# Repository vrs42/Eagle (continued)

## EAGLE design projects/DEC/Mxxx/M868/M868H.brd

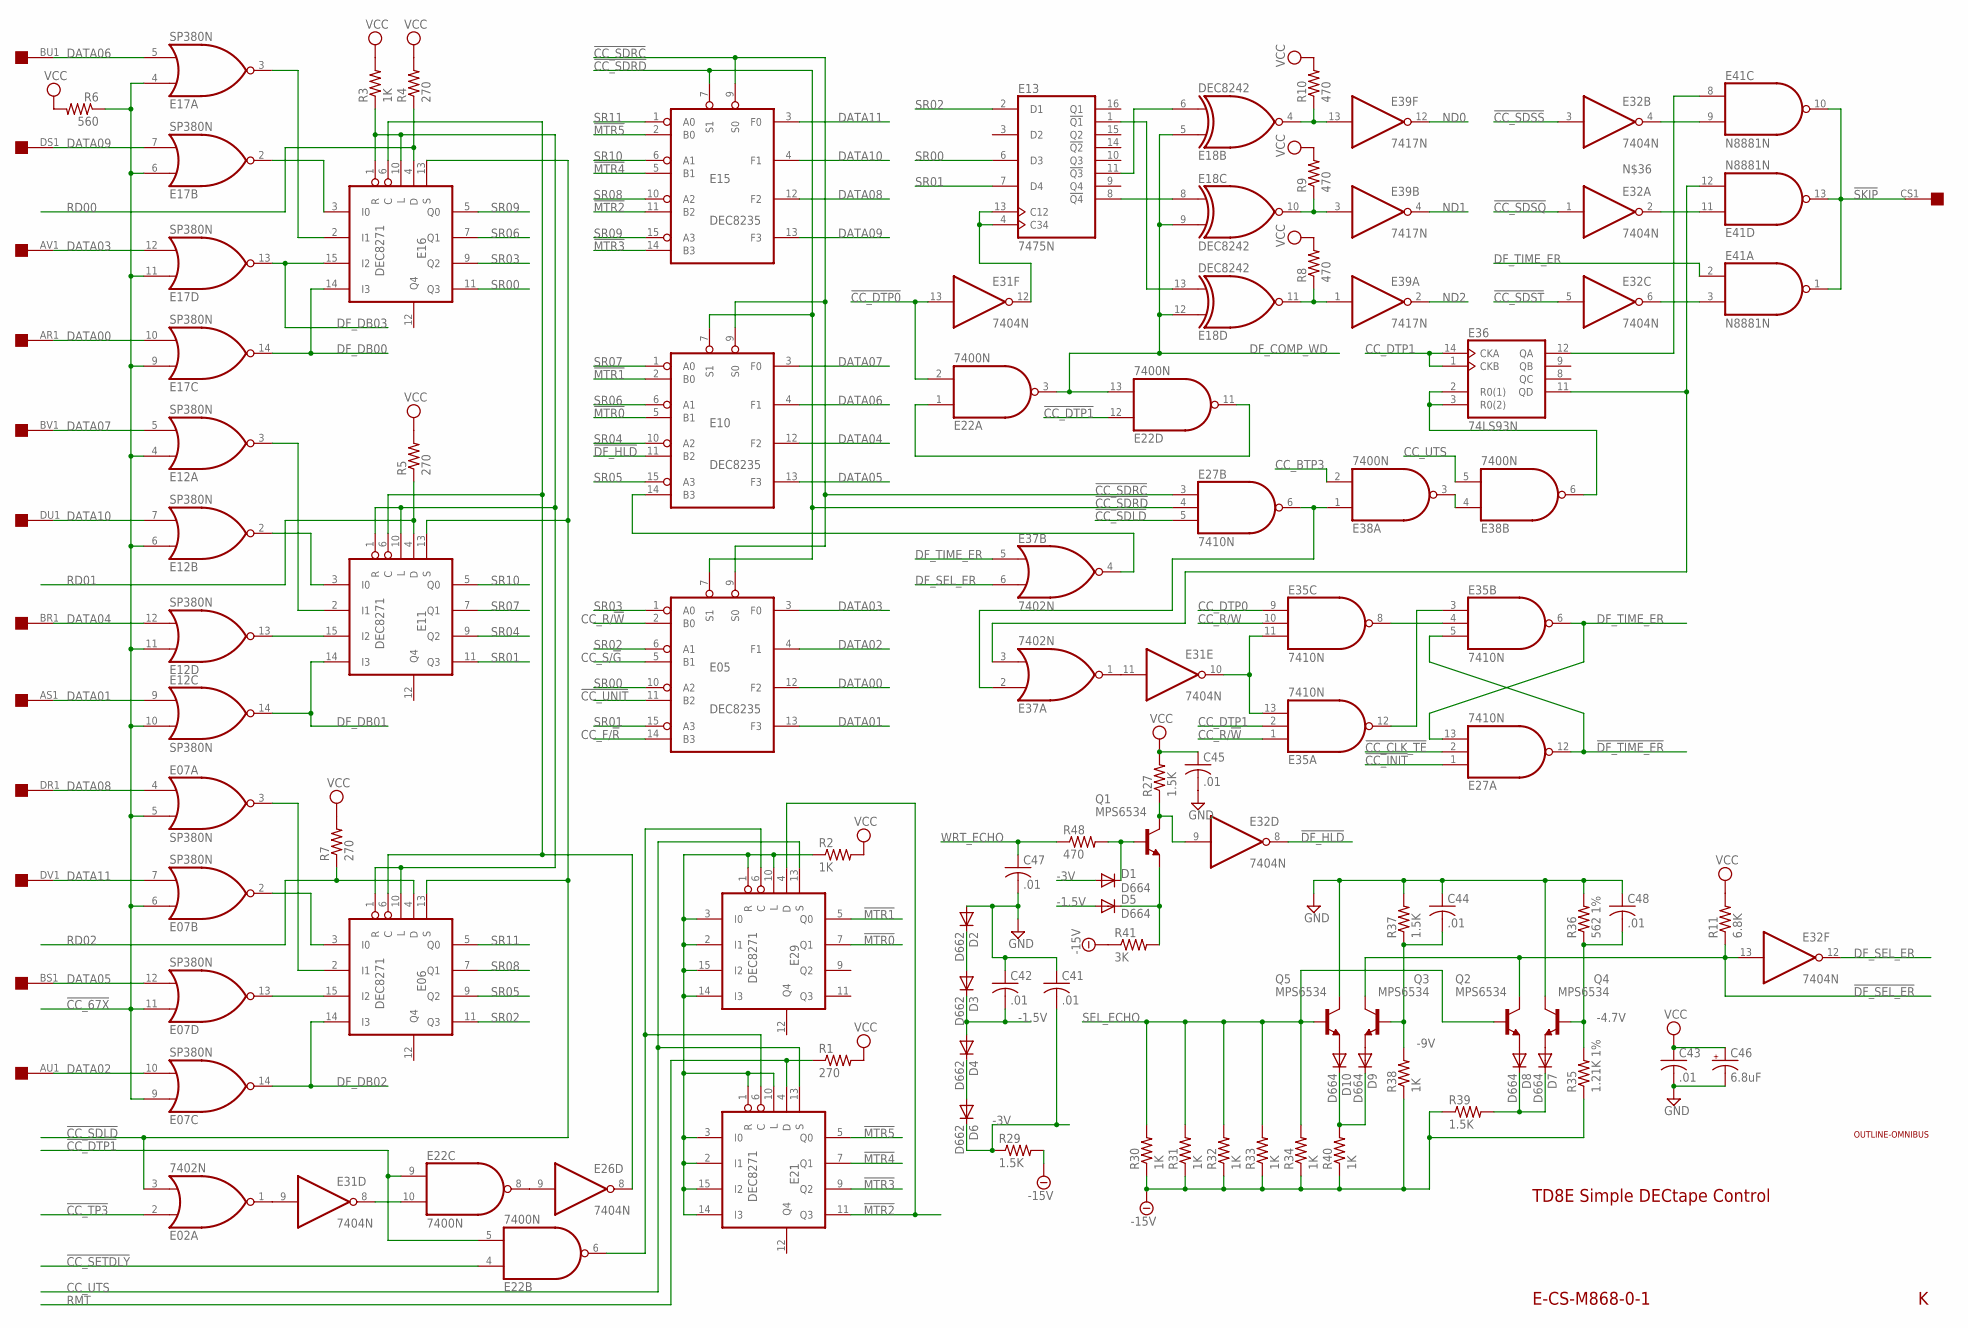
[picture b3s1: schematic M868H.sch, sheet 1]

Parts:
C41, C42, C43, C44, C45, C47, C48: .01; C050-025X075
C46: 6.8uF; E12-8
D1, D5, D7, D8, D9, D10: D664; DO35-10
D2, D3, D4, D6: D662; DO35-10
E02, E37: 7402N; DIL14
E05, E10, E15: DEC8235; DIL16
E06, E11, E16, E21, E29: DEC8271; DIL16
E07, E12, E17: SP380N; DIL14
E13: 7475N; DIL16
E18: DEC8242; DIL14
E22, E38: 7400N; DIL14
E26, E31, E32: 7404N; DIL14
E27, E35: 7410N; DIL14
E36: 74LS93N; DIL14
E39: 7417N; DIL14
E41: N8881N; DIL14
EDGE$: QUAD; EDGE-CON8
Q1, Q2, Q3, Q4, Q5: MPS6534; TO5
R1, R4, R5, R7: 270; 0207/10
R2, R3, R30, R31, R32, R33, R34, R38, R40: 1K; 0207/10
R6: 560; 0207/10
R8, R9, R10, R48: 470; 0207/10
R11: 6.8K; 0207/10
R27, R29, R37, R39: 1.5K; 0207/10
R35: 1.21K 1%; 0207/15
R36: 562 1%; 0207/15
R41: 3K; 0207/10
U$1: OUTLINE-OMNIBUS; OMNIBUS

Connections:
!CC_67X: E07.5 (I1), E07.6 (I0), E07.9 (I0), E07.11 (I0), E12.4 (I0), E12.6 (I0), E12.10 (I1), E12.11 (I0), E17.4 (I0), E17.6 (I0), E17.9 (I0), E17.11 (I0), R6.1; also elsewhere on the board
!CC_CLK_TE: E27.2 (I1); also elsewhere on the board
!CC_DTP0: E22.2 (I1), E31.13 (I); also elsewhere on the board
!CC_DTP1: E22.5 (I1), E22.9 (I0), E22.12 (I0); also elsewhere on the board
!CC_INIT: E27.1 (I0); also elsewhere on the board
!CC_SDLD: E02.3 (I1), E06.13 (S), E11.13 (S), E16.13 (S), E27.5 (I2); also elsewhere on the board
!CC_SDRC: E05.9 (S0), E10.9 (S0), E15.9 (S0), E27.3 (I0); also elsewhere on the board
!CC_SDRD: E05.7 (S1), E10.7 (S1), E15.7 (S1), E27.4 (I1); also elsewhere on the board
!CC_SDSQ: E32.1 (I); also elsewhere on the board
!CC_SDSS: E32.3 (I); also elsewhere on the board
!CC_SDST: E32.5 (I); also elsewhere on the board
!CC_SETDLY: E22.4 (I0); also elsewhere on the board
!CC_TP3: E02.2 (I0); also elsewhere on the board
!CC_UNIT: E05.11 (B2); also elsewhere on the board
!DF_HLD: E10.11 (B2), E32.8 (O); also elsewhere on the board
!DF_SEL_ER: E32.13 (I), Q2.3 (C), Q3.3 (C), R11.1; also elsewhere on the board
!DF_TIME_ER: E27.12 (O), E35.5 (I2); also elsewhere on the board
!MTR0: E10.5 (B1), E29.7 (Q1)
!MTR1: E10.2 (B0), E29.5 (Q0)
!MTR2: E15.11 (B2), E21.11 (Q3), E29.4 (D)
!MTR3: E15.14 (B3), E21.9 (Q2)
!MTR4: E15.5 (B1), E21.7 (Q1)
!MTR5: E15.2 (B0), E21.5 (Q0)
!SKIP: E41.1 (O), E41.10 (O), E41.13 (O), EDGE$.CS1
-1.5V: C42.2, D3.C, D4.A, D5.A
-3V: C41.2, D1.A, D6.C, R29.1
-4.7V: C48.2, Q4.2 (B), R35.2, R36.1
-9V: C44.2, Q3.2 (B), R37.1, R38.2
-15V: R29.2, R30.1, R31.1, R32.1, R33.1, R34.1, R35.1, R38.1, R39.1, R40.1, R41.1; also elsewhere on the board
CC_BTP3: E38.2 (I1); also elsewhere on the board
CC_DTP0: E35.9 (I0); also elsewhere on the board
CC_DTP1: E35.2 (I1), E36.1 (CKB), E36.14 (CKA); also elsewhere on the board
CC_F/!R: E05.14 (B3); also elsewhere on the board
CC_R/!W: E05.2 (B0), E35.1 (I0); also elsewhere on the board
CC_R/W: E35.10 (I1); also elsewhere on the board
CC_S/!G: E05.5 (B1); also elsewhere on the board
CC_UTS: E21.13 (S), E29.13 (S), E38.5 (I1); also elsewhere on the board
DATA00: E05.12 (F2), E17.10 (I1), EDGE$.AR1
DATA01: E05.13 (F3), E12.9 (I0), EDGE$.AS1
DATA02: E05.4 (F1), E07.10 (I1), EDGE$.AU1
DATA03: E05.3 (F0), E17.12 (I1), EDGE$.AV1
DATA04: E10.12 (F2), E12.12 (I1), EDGE$.BR1
DATA05: E07.12 (I1), E10.13 (F3), EDGE$.BS1
DATA06: E10.4 (F1), E17.5 (I1), EDGE$.BU1
DATA07: E10.3 (F0), E12.5 (I1), EDGE$.BV1
DATA08: E07.4 (I0), E15.12 (F2), EDGE$.DR1
DATA09: E15.13 (F3), E17.7 (I1), EDGE$.DS1
DATA10: E12.7 (I1), E15.4 (F1), EDGE$.DU1
DATA11: E07.7 (I1), E15.3 (F0), EDGE$.DV1
DF_COMP_WD: E18.5 (I0), E18.9 (I1), E18.12 (I0), E22.3 (O), E22.13 (I1)
DF_DB00: E16.14 (I3), E17.14 (O); also elsewhere on the board
DF_DB01: E11.14 (I3), E12.14 (O); also elsewhere on the board
DF_DB02: E06.14 (I3), E07.14 (O); also elsewhere on the board
DF_DB03: E16.15 (I2), E17.13 (O); also elsewhere on the board
DF_SEL_ER: E32.12 (O), E37.6 (I1)
DF_TIME_ER: E27.13 (I2), E35.6 (O), E37.5 (I0), E41.2 (I0)
GND: C41.1, C42.1, C43.2, C44.1, C45.2, C46.-, C47.2, C48.1, D2.A, E02.7 (GND), E05.8 (GND), E06.8 (GND), E07.1 (GND), E10.8 (GND), E11.8 (GND), E12.1 (GND), E13.12 (GND), E15.8 (GND), E16.8 (GND), E17.1 (GND), E18.7 (GND), E21.8 (GND), E22.7 (GND), E26.7 (GND), E27.7 (GND), E29.8 (GND), E31.7 (GND), E32.7 (GND), E35.7 (GND), E36.10 (GND), E37.7 (GND), E38.7 (GND), E39.7 (GND), E41.7 (GND), Q4.3 (C), Q5.3 (C), R36.2, R37.2; also elsewhere on the board
unnamed: E06.1 (R), E06.10 (L), E11.1 (R), E11.10 (L), E16.1 (R), E16.10 (L), R3.1
unnamed: E02.1 (O), E31.9 (I)
unnamed: E16.2 (I1), E17.3 (O)
unnamed: E16.3 (I0), E17.2 (O)
unnamed: E21.1 (R), E21.2 (I1), E21.3 (I0), E21.10 (L), E21.14 (I3), E21.15 (I2), E29.1 (R), E29.2 (I1), E29.3 (I0), E29.10 (L), E29.14 (I3), E29.15 (I2), R2.1
unnamed: E06.6 (C), E11.6 (C), E16.6 (C), E26.8 (O)
unnamed: E11.2 (I1), E12.3 (O)
unnamed: E11.3 (I0), E12.2 (O)
unnamed: E13.11 (!Q3), E18.6 (I1)
unnamed: E11.15 (I2), E12.13 (O)
unnamed: E06.2 (I1), E07.3 (O)
unnamed: E06.3 (I0), E07.2 (O)
unnamed: E06.15 (I2), E07.13 (O)
unnamed: E27.6 (O), E37.2 (I0), E38.1 (I0)
unnamed: E36.12 (QA), E41.8 (I0)
unnamed: E22.8 (O), E26.9 (I)
unnamed: E22.10 (I1), E31.8 (O)
unnamed: E21.6 (C), E22.6 (O), E29.6 (C)
unnamed: E13.1 (!Q1), E18.13 (I1)
unnamed: E18.11 (O), E39.1 (I), R8.1
unnamed: E13.8 (!Q4), E18.8 (I0)
unnamed: E13.4 (C34), E13.13 (C12), E31.12 (O)
unnamed: E36.11 (QD), E37.3 (I1), E41.12 (I1)
unnamed: E22.1 (I0), E22.11 (O)
unnamed: E18.10 (O), E39.3 (I), R9.1
unnamed: E18.4 (O), E39.13 (I), R10.1
unnamed: E10.14 (B3), E37.4 (O)
unnamed: E36.2 (R0(1)), E36.3 (R0(2)), E38.6 (O)
unnamed: E38.3 (O), E38.4 (I0)
unnamed: E32.6 (O), E41.3 (I1)
unnamed: E32.2 (O), E41.11 (I0)
unnamed: E32.4 (O), E41.9 (I1)
unnamed: E31.11 (I), E37.1 (O)
unnamed: E31.10 (O), E35.11 (I2), E35.13 (I2)
unnamed: E35.3 (I0), E35.12 (O)
unnamed: E35.4 (I1), E35.8 (O)
unnamed: D1.C, Q1.2 (B), R48.2
unnamed: D5.C, Q1.1 (E), R41.2
unnamed: E32.9 (I), Q1.3 (C), R27.1
unnamed: D2.C, D3.A
unnamed: D9.C, D10.C, R40.2
unnamed: D4.C, D6.A
unnamed: D10.A, Q5.1 (E)
unnamed: D9.A, Q3.1 (E)
unnamed: D8.A, Q2.1 (E)
unnamed: D7.A, Q4.1 (E)
unnamed: D7.C, D8.C, R39.2
ND0: E39.12 (O); also elsewhere on the board
ND1: E39.4 (O); also elsewhere on the board
ND2: E39.2 (O); also elsewhere on the board
RD00: E16.4 (D), R4.1; also elsewhere on the board
RD01: E11.4 (D), R5.1; also elsewhere on the board
RD02: E06.4 (D), R7.1; also elsewhere on the board
RMT: E21.4 (D), R1.1; also elsewhere on the board
SEL_ECHO: Q2.2 (B), Q5.2 (B), R30.2, R31.2, R32.2, R33.2, R34.2; also elsewhere on the board
SR00: E05.10 (A2), E13.6 (D3), E16.11 (Q3)
SR01: E05.15 (A3), E11.11 (Q3), E13.7 (D4)
SR02: E05.6 (A1), E06.11 (Q3), E13.2 (D1)
SR03: E05.1 (A0), E16.9 (Q2)
SR04: E10.10 (A2), E11.9 (Q2)
SR05: E06.9 (Q2), E10.15 (A3)
SR06: E10.6 (A1), E16.7 (Q1)
SR07: E10.1 (A0), E11.7 (Q1)
SR08: E06.7 (Q1), E15.10 (A2)
SR09: E15.15 (A3), E16.5 (Q0)
SR10: E11.5 (Q0), E15.6 (A1)
SR11: E06.5 (Q0), E15.1 (A0)
VCC: C43.1, C45.1, C46.+, E02.14 (VCC), E05.16 (VCC), E06.16 (VCC), E07.8 (VCC), E10.16 (VCC), E11.16 (VCC), E12.8 (VCC), E13.5 (VCC), E15.16 (VCC), E16.16 (VCC), E17.8 (VCC), E18.14 (VCC), E21.16 (VCC), E22.14 (VCC), E26.14 (VCC), E27.14 (VCC), E29.16 (VCC), E31.14 (VCC), E32.14 (VCC), E35.14 (VCC), E36.5 (VCC), E37.14 (VCC), E38.14 (VCC), E39.14 (VCC), E41.14 (VCC), R1.2, R2.2, R3.2, R4.2, R5.2, R6.2, R7.2, R8.2, R9.2, R10.2, R11.2, R27.2; also elsewhere on the board
WRT_ECHO: C47.1, R48.1; also elsewhere on the board

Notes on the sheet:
E-CS-M868-0-1
TD8E Simple DECtape Control

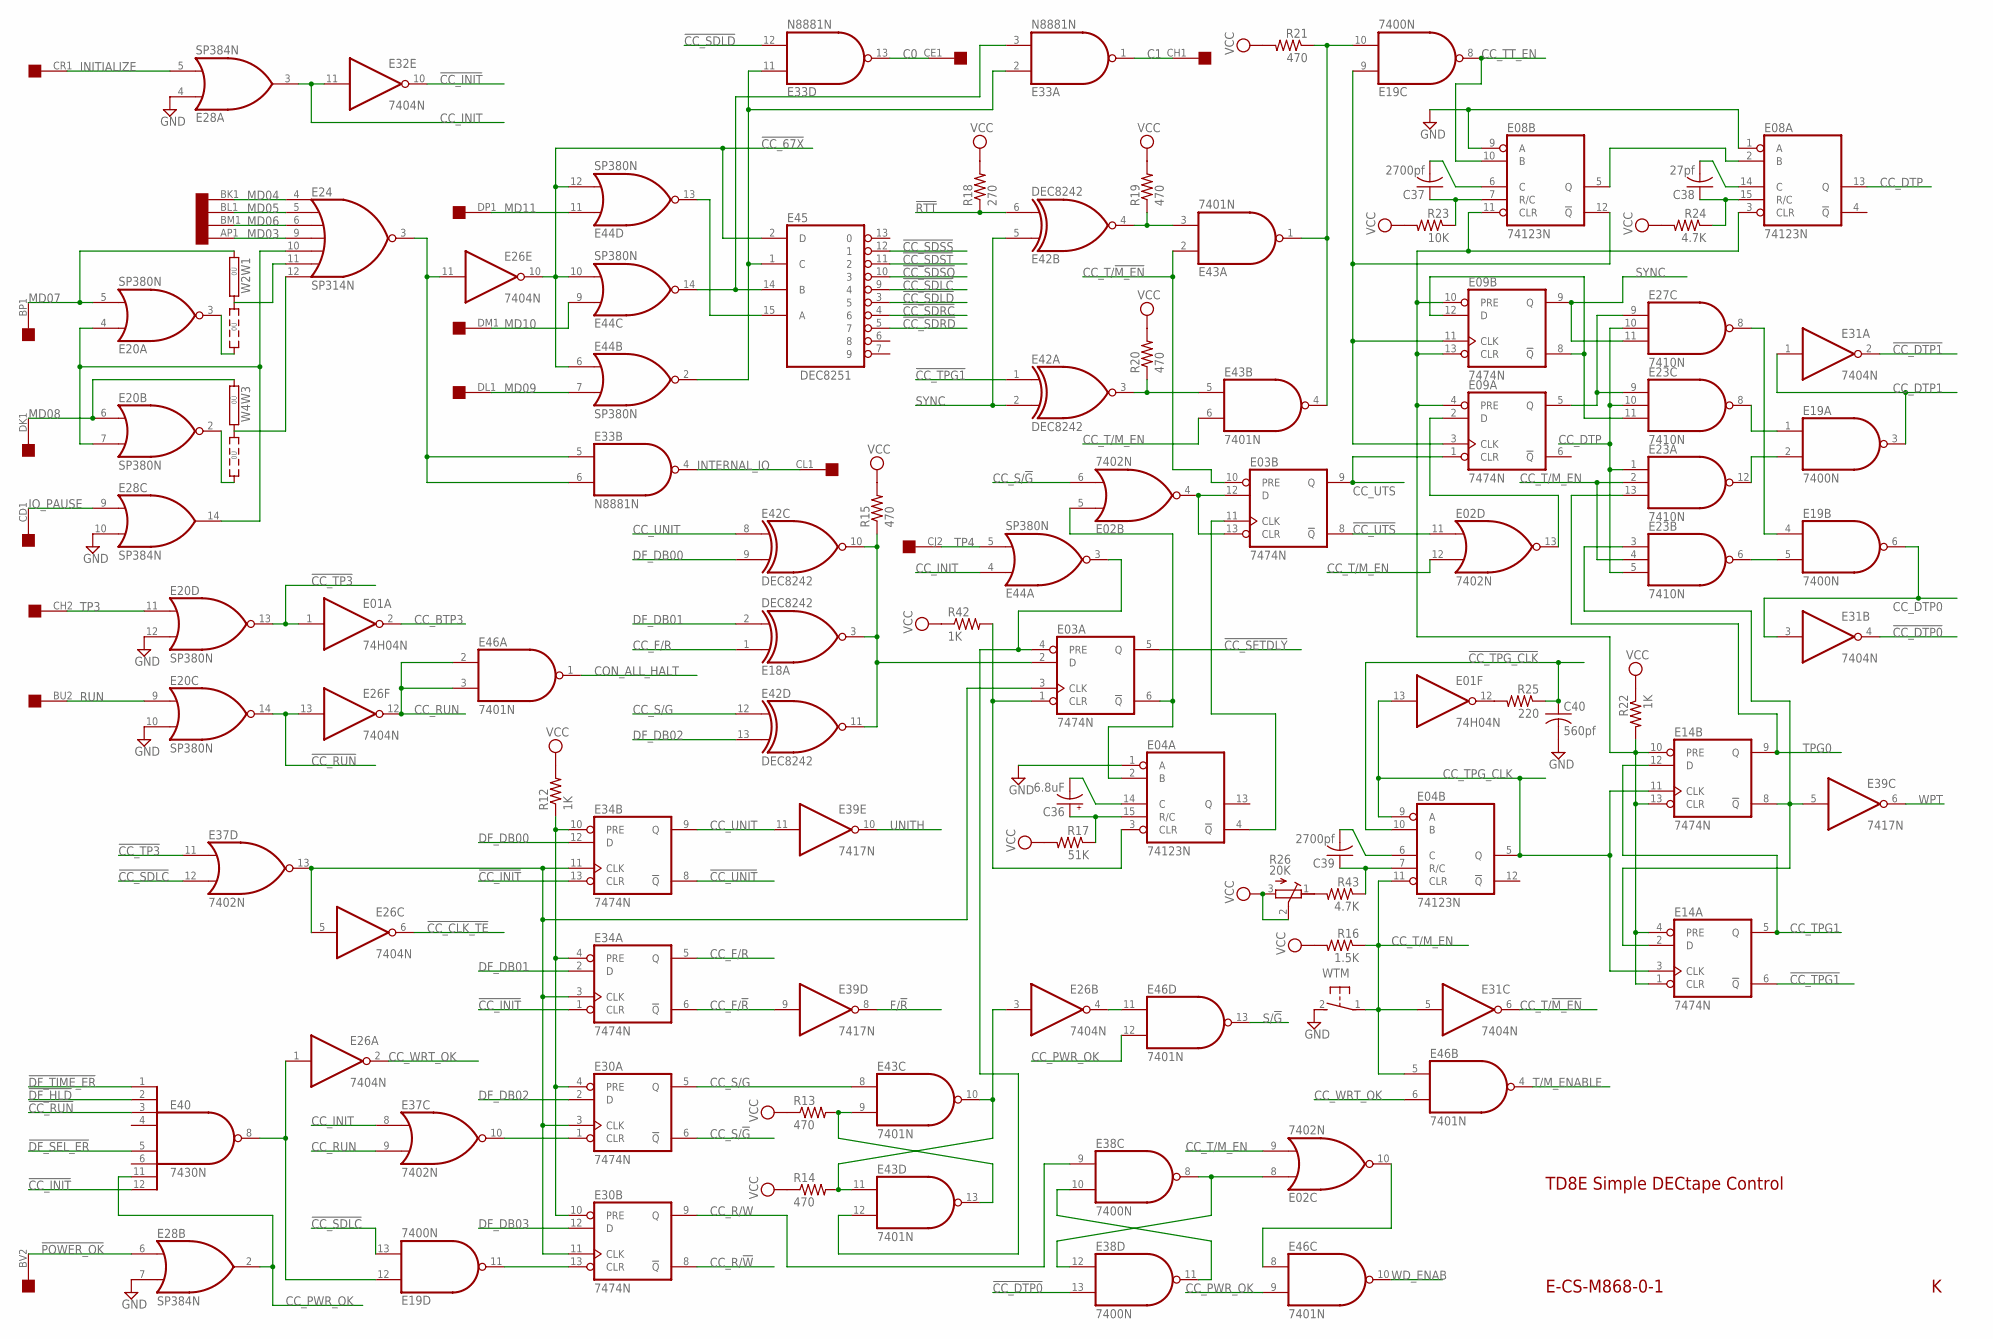
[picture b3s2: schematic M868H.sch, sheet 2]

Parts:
C36: 6.8uF; E12-8
C37, C39: 2700pf; C102-043X133
C38: 27pf; C050-025X075
C40: 560pf; C075-032X103
E01: 74H04N; DIL14
E02, E37: 7402N; DIL14
E03, E09, E14, E30, E34: 7474N; DIL14
E04, E08: 74123N; DIL16
E18, E42: DEC8242; DIL14
E19, E38: 7400N; DIL14
E20, E44: SP380N; DIL14
E23, E27: 7410N; DIL14
E24: SP314N; DIL14
E26, E31, E32: 7404N; DIL14
E28: SP384N; DIL14
E33: N8881N; DIL14
E39: 7417N; DIL14
E40: 7430N; DIL14
E43, E46: 7401N; DIL14
E45: DEC8251; DIL16
EDGE$: QUAD; EDGE-CON8
R12, R22, R42: 1K; 0207/10
R13, R14, R15, R19, R20, R21: 470; 0207/10
R16: 1.5K; 0207/10
R17: 51K; 0207/10
R18: 270; 0207/10
R23: 10K; 0207/10
R24, R43: 4.7K; 0207/10
R25: 220; 0207/10
R26: 20K; 3006Y
W2W1, W4W3: 0R2; 0R2/10
WTM: 31-XX; B3F-31XX

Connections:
!CC_67X: E26.10 (O), E44.6 (I0), E44.10 (I1), E44.12 (I1), E45.2 (D); also elsewhere on the board
!CC_CLK_TE: E26.6 (O); also elsewhere on the board
!CC_DTP0: E31.4 (O), E38.13 (I1); also elsewhere on the board
!CC_DTP1: E31.2 (O); also elsewhere on the board
!CC_INIT: E32.10 (O), E34.1 (CLR), E34.13 (CLR), E40.12 (I7); also elsewhere on the board
!CC_RUN: E20.14 (O), E26.13 (I), E40.3 (I2)
!CC_SDLC: E19.13 (I1), E37.12 (I1), E45.9 (4)
!CC_SDLD: E33.12 (I1), E45.3 (5); also elsewhere on the board
!CC_SDRC: E45.4 (6); also elsewhere on the board
!CC_SDRD: E45.5 (7); also elsewhere on the board
!CC_SDSQ: E45.10 (3); also elsewhere on the board
!CC_SDSS: E45.12 (1); also elsewhere on the board
!CC_SDST: E45.11 (2); also elsewhere on the board
!CC_SETDLY: E03.5 (Q); also elsewhere on the board
!CC_TP3: E01.1 (I), E20.13 (O), E37.11 (I0); also elsewhere on the board
!CC_TPG1: E14.6 (!Q), E42.1 (I0)
!CC_TPG_CLK: C40.1, E04.10 (B), R25.1
!CC_UNIT: E34.8 (!Q); also elsewhere on the board
!CC_UTS: E02.11 (I0), E03.8 (!Q)
!DF_HLD: E40.2 (I1); also elsewhere on the board
!DF_SEL_ER: E40.5 (I4); also elsewhere on the board
!DF_TIME_ER: E40.1 (I0); also elsewhere on the board
!IO_PAUSE: E20.4 (I0), E20.7 (I1), E24.10 (I4), E28.14 (O)
!POWER_OK: E28.6 (I0), EDGE$.BV2
!RTT: E42.6 (I1), R18.1; also elsewhere on the board
C0: E33.13 (O), EDGE$.CE1
C1: E33.1 (O), EDGE$.CH1
CC_67X: E24.3 (O), E26.11 (I), E33.5 (I0), E33.6 (I1)
CC_BTP3: E01.2 (O); also elsewhere on the board
CC_DTP: E08.13 (Q), E23.1 (I0), E23.5 (I2), E23.10 (I1), E27.10 (I1)
CC_DTP0: E19.6 (O), E31.3 (I); also elsewhere on the board
CC_DTP1: E19.3 (O), E31.1 (I); also elsewhere on the board
CC_F/!R: E34.6 (!Q), E39.9 (I); also elsewhere on the board
CC_F/R: E18.1 (I0), E34.5 (Q)
CC_INIT: E28.3 (O), E32.11 (I), E37.8 (I0), E44.4 (I0)
CC_PWR_OK: E28.2 (O), E40.11 (I6), E46.9 (I1), E46.12 (I1)
CC_R/!W: E30.8 (!Q); also elsewhere on the board
CC_R/W: E30.9 (Q), E38.9 (I0); also elsewhere on the board
CC_RUN: E26.12 (O), E37.9 (I1), E46.2 (I0), E46.3 (I1)
CC_S/!G: E02.6 (I1), E30.6 (!Q); also elsewhere on the board
CC_S/G: E30.5 (Q), E42.12 (I0), E43.8 (I0)
CC_SETDLY: E02.5 (I0), E03.6 (!Q), E04.2 (B)
CC_T/!M_EN: E03.10 (PRE), E31.6 (O), E43.2 (I0)
CC_T/M_EN: E02.9 (I1), E02.12 (I1), E04.11 (CLR), E23.2 (I1), E23.4 (I1), E31.5 (I), E43.6 (I1), E46.5 (I0), R16.1, WTM.1
CC_TPG1: E14.5 (Q), E14.12 (D)
CC_TPG_CLK: E01.13 (I), E04.5 (Q), E04.9 (A), E14.3 (CLK), E14.11 (CLK)
CC_TT_EN: E08.10 (B), E19.8 (O)
CC_UNIT: E34.9 (Q), E39.11 (I), E42.8 (I0)
CC_UTS: E03.9 (Q), E09.1 (CLR); also elsewhere on the board
CC_WRT_OK: E26.2 (O), E46.6 (I1)
CON_ALL_HALT: E46.1 (O); also elsewhere on the board
DF_DB00: E34.12 (D), E42.9 (I1); also elsewhere on the board
DF_DB01: E18.2 (I1), E34.2 (D); also elsewhere on the board
DF_DB02: E30.2 (D), E42.13 (I1); also elsewhere on the board
DF_DB03: E30.12 (D); also elsewhere on the board
F/!R: E39.8 (O); also elsewhere on the board
GND: C40.2, E01.7 (GND), E02.7 (GND), E03.7 (GND), E04.1 (A), E04.8 (GND), E08.1 (A), E08.8 (GND), E08.9 (A), E09.7 (GND), E14.7 (GND), E18.7 (GND), E19.7 (GND), E20.1 (GND), E20.10 (I1), E20.12 (I1), E23.7 (GND), E24.1 (GND), E26.7 (GND), E27.7 (GND), E28.1 (GND), E28.4 (I0), E28.7 (I1), E28.10 (I1), E30.7 (GND), E31.7 (GND), E32.7 (GND), E33.7 (GND), E34.7 (GND), E37.7 (GND), E38.7 (GND), E39.7 (GND), E40.7 (GND), E42.7 (GND), E43.7 (GND), E44.1 (GND), E45.8 (GND), E46.7 (GND), WTM.2 (S); also elsewhere on the board
INITIALIZE: E28.5 (I1), EDGE$.CR1
INTERNAL_IO: E33.4 (O), EDGE$.CL1
IO_PAUSE: E28.9 (I0), EDGE$.CD1
MD03: E24.9 (I3), EDGE$.AP1
MD04: E24.4 (I0), EDGE$.BK1
MD05: E24.5 (I1), EDGE$.BL1
MD06: E24.6 (I2), EDGE$.BM1
MD07: E20.5 (I1), EDGE$.BP1, W2W1.1
MD08: E20.6 (I0), EDGE$.DK1, W4W3.1
MD09: E44.7 (I1), EDGE$.DL1
MD10: E44.9 (I0), EDGE$.DM1
MD11: E44.11 (I0), EDGE$.DP1
unnamed: E43.9 (I1), E43.13 (O), R13.2
unnamed: E08.3 (CLR), E08.11 (CLR), E09.4 (PRE), E09.10 (PRE), E09.13 (CLR), E14.1 (CLR), E14.4 (PRE), E14.10 (PRE), E14.13 (CLR), R22.2
unnamed: E30.1 (CLR), E37.10 (O)
unnamed: E26.3 (I), E43.10 (O), E43.11 (I0), R14.2
unnamed: E24.11 (I5), W2W1.2
unnamed: E24.12 (I6), W4W3.2
unnamed: E20.3 (O), W2W1.3
unnamed: E19.12 (I0), E26.1 (I), E40.8 (O)
unnamed: E20.2 (O), W4W3.3
unnamed: E19.11 (O), E30.13 (CLR)
unnamed: E33.2 (I0), E33.11 (I0), E44.2 (O), E45.1 (C)
unnamed: E33.3 (I1), E44.14 (O), E45.14 (B)
unnamed: E44.13 (O), E45.15 (A)
unnamed: E42.4 (O), E43.3 (I1), R19.1
unnamed: E19.10 (I1), E43.1 (O), E43.4 (O), R21.1
unnamed: E42.3 (O), E43.5 (I0), R20.1
unnamed: E08.2 (B), E08.5 (Q)
unnamed: C37.1, E08.7 (R/C), R23.1
unnamed: C38.1, E08.15 (R/C), R24.1
unnamed: E08.12 (!Q), E09.3 (CLK), E09.11 (CLK), E19.9 (I0)
unnamed: C38.2, E08.14 (C)
unnamed: C37.2, E08.6 (C)
unnamed: E03.3 (CLK), E26.5 (I), E30.3 (CLK), E30.11 (CLK), E34.3 (CLK), E34.11 (CLK), E37.13 (O)
unnamed: E30.4 (PRE), E30.10 (PRE), E34.4 (PRE), E34.10 (PRE), R12.1
unnamed: E38.10 (I1), E38.11 (O)
unnamed: E02.8 (I0), E38.8 (O), E38.12 (I0)
unnamed: E03.4 (PRE), E43.12 (I1), E44.3 (O)
unnamed: E26.4 (O), E46.11 (I0)
unnamed: E02.10 (O), E46.8 (I0)
unnamed: E03.2 (D), E18.3 (O), E42.10 (O), E42.11 (O), R15.1
unnamed: E03.1 (CLR), E04.3 (CLR), R42.2
unnamed: C36.+, E04.15 (R/C), R17.1
unnamed: C36.-, E04.14 (C)
unnamed: E03.11 (CLK), E04.4 (!Q)
unnamed: E02.4 (O), E03.12 (D), E03.13 (CLR)
unnamed: E02.13 (O), E09.2 (D)
unnamed: E19.5 (I1), E23.6 (O)
unnamed: E09.5 (Q), E23.9 (I0), E27.9 (I0)
unnamed: E09.8 (!Q), E09.12 (D), E23.11 (I2)
unnamed: E19.2 (I1), E23.12 (O)
unnamed: E19.1 (I0), E23.8 (O)
unnamed: E14.2 (D), E14.8 (!Q), E23.3 (I0), E39.5 (I)
unnamed: C39.1, E04.7 (R/C), R43.1
unnamed: E19.4 (I0), E27.8 (O)
unnamed: C39.2, E04.6 (C)
unnamed: R26.1 (A), R43.2
unnamed: E01.12 (O), R25.2
RUN: E20.9 (I0), EDGE$.BU2
S/!G: E46.13 (O); also elsewhere on the board
SYNC: E09.9 (Q), E27.11 (I2), E42.2 (I1), E42.5 (I0)
T/M_ENABLE: E46.4 (O); also elsewhere on the board
TP3: E20.11 (I0), EDGE$.CH2
TP4: E44.5 (I1), EDGE$.CJ2
TPG0: E14.9 (Q), E23.13 (I2)
UNITH: E39.10 (O); also elsewhere on the board
VCC: E01.14 (VCC), E02.14 (VCC), E03.14 (VCC), E04.16 (VCC), E08.16 (VCC), E09.14 (VCC), E14.14 (VCC), E18.14 (VCC), E19.14 (VCC), E20.8 (VCC), E23.14 (VCC), E24.8 (VCC), E26.14 (VCC), E27.14 (VCC), E28.8 (VCC), E30.14 (VCC), E31.14 (VCC), E32.14 (VCC), E33.14 (VCC), E34.14 (VCC), E37.14 (VCC), E38.14 (VCC), E39.14 (VCC), E40.14 (VCC), E42.14 (VCC), E43.14 (VCC), E44.8 (VCC), E45.16 (VCC), E46.14 (VCC), R12.2, R13.1, R14.1, R15.2, R16.2, R17.2, R18.2, R19.2, R20.2, R21.2, R22.1, R23.2, R24.2, R26.2 (S), R26.3 (E), R42.1; also elsewhere on the board
WD_ENAB: E46.10 (O); also elsewhere on the board
WPT: E39.6 (O); also elsewhere on the board

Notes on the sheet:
E-CS-M868-0-1
TD8E Simple DECtape Control

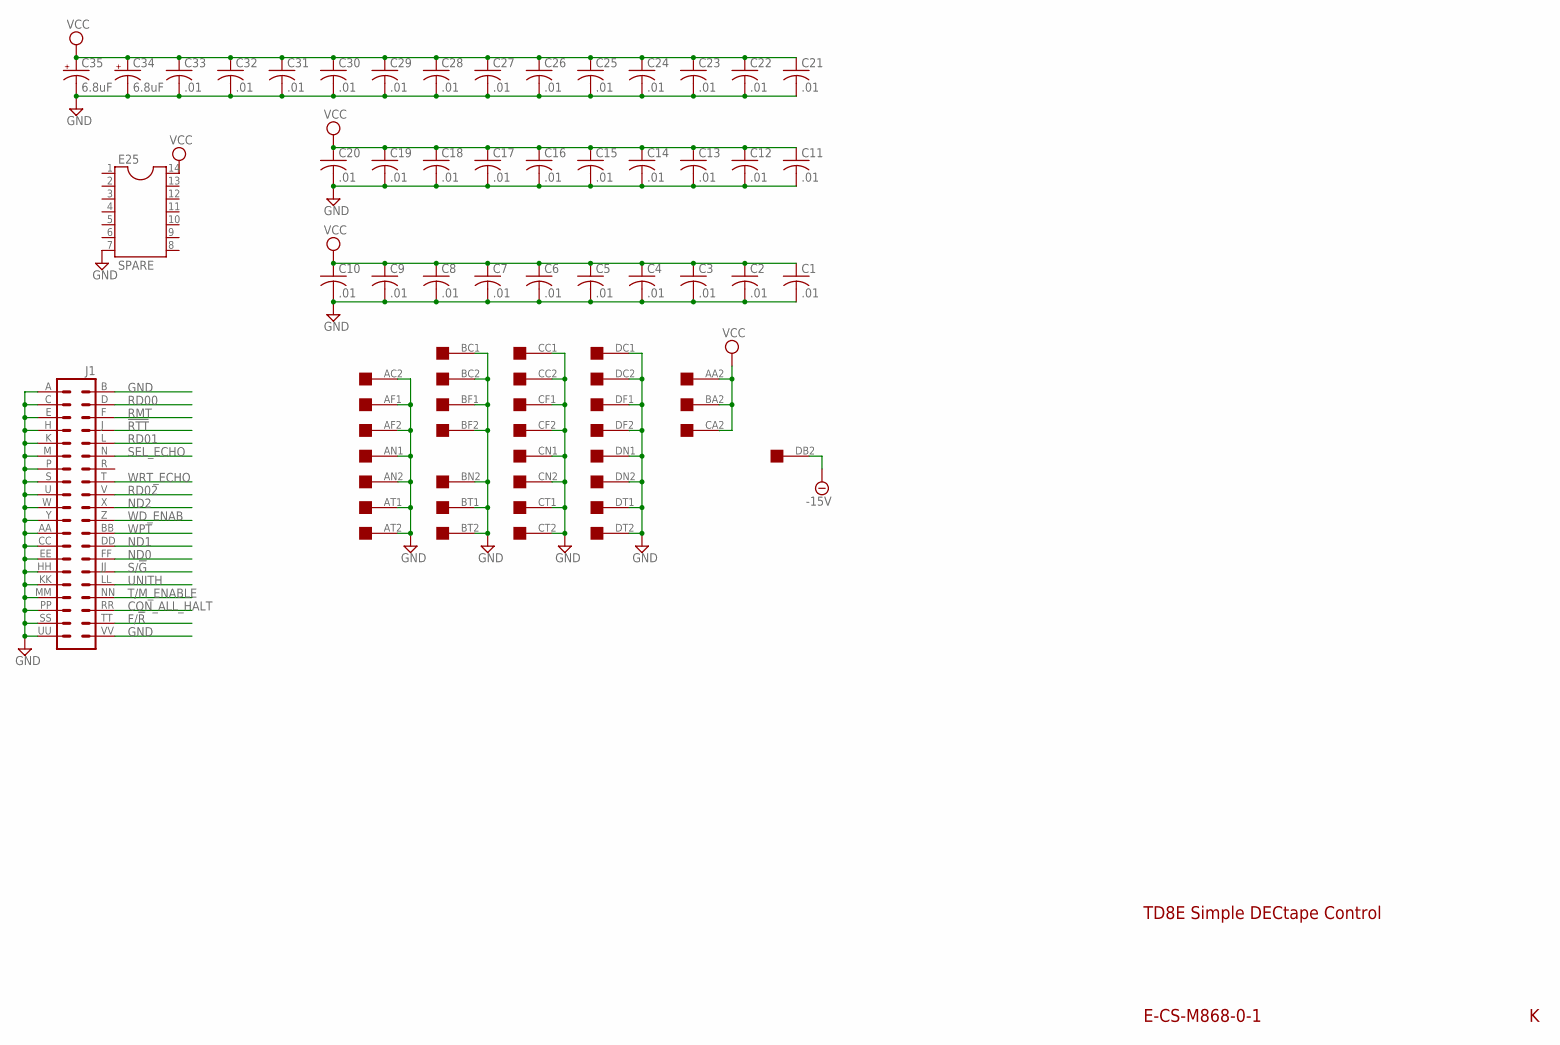
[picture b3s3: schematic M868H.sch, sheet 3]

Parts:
C1, C2, C3, C4, C5, C6, C7, C8, C9, C10, C11, C12, C13, C14, C15, C16, C17, C18, C19, C20, C21, C22, C23, C24, C25, C26, C27, C28, C29, C30, C31, C32, C33: .01; C050-025X075
C34, C35: 6.8uF; E12-8
E25: SPARE; DIL14
EDGE$: QUAD; EDGE-CON8
J1: DEC40PINH

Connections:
!RTT: J1.J (8); also elsewhere on the board
-15V: EDGE$.DB2; also elsewhere on the board
CON_ALL_HALT: J1.RR (36); also elsewhere on the board
F/!R: J1.TT (38); also elsewhere on the board
GND: C1.2, C2.2, C3.2, C4.2, C5.2, C6.2, C7.2, C8.2, C9.2, C10.2, C11.2, C12.2, C13.2, C14.2, C15.2, C16.2, C17.2, C18.2, C19.2, C20.2, C21.2, C22.2, C23.2, C24.2, C25.2, C26.2, C27.2, C28.2, C29.2, C30.2, C31.2, C32.2, C33.2, C34.-, C35.-, E25.7, EDGE$.AC2, EDGE$.AF1, EDGE$.AF2, EDGE$.AN1, EDGE$.AN2, EDGE$.AT1, EDGE$.AT2, EDGE$.BC1, EDGE$.BC2, EDGE$.BF1, EDGE$.BF2, EDGE$.BN2, EDGE$.BT1, EDGE$.BT2, EDGE$.CC1, EDGE$.CC2, EDGE$.CF1, EDGE$.CF2, EDGE$.CN1, EDGE$.CN2, EDGE$.CT1, EDGE$.CT2, EDGE$.DC1, EDGE$.DC2, EDGE$.DF1, EDGE$.DF2, EDGE$.DN1, EDGE$.DN2, EDGE$.DT1, EDGE$.DT2, J1.A (1), J1.AA (23), J1.B (2), J1.C (3), J1.CC (25), J1.E (5), J1.EE (27), J1.H (7), J1.HH (29), J1.K (9), J1.KK (31), J1.M (11), J1.MM (33), J1.P (13), J1.PP (35), J1.S (15), J1.SS (37), J1.U (17), J1.UU (39), J1.VV (40), J1.W (19), J1.Y (21); also elsewhere on the board
ND0: J1.FF (28); also elsewhere on the board
ND1: J1.DD (26); also elsewhere on the board
ND2: J1.X (20); also elsewhere on the board
RD00: J1.D (4); also elsewhere on the board
RD01: J1.L (10); also elsewhere on the board
RD02: J1.V (18); also elsewhere on the board
RMT: J1.F (6); also elsewhere on the board
S/!G: J1.JJ (30); also elsewhere on the board
SEL_ECHO: J1.N (12); also elsewhere on the board
T/M_ENABLE: J1.NN (34); also elsewhere on the board
UNITH: J1.LL (32); also elsewhere on the board
VCC: C1.1, C2.1, C3.1, C4.1, C5.1, C6.1, C7.1, C8.1, C9.1, C10.1, C11.1, C12.1, C13.1, C14.1, C15.1, C16.1, C17.1, C18.1, C19.1, C20.1, C21.1, C22.1, C23.1, C24.1, C25.1, C26.1, C27.1, C28.1, C29.1, C30.1, C31.1, C32.1, C33.1, C34.+, C35.+, E25.14, EDGE$.AA2, EDGE$.BA2, EDGE$.CA2; also elsewhere on the board
WD_ENAB: J1.Z (22); also elsewhere on the board
WPT: J1.BB (24); also elsewhere on the board
WRT_ECHO: J1.T (16); also elsewhere on the board

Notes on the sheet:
E-CS-M868-0-1
TD8E Simple DECtape Control

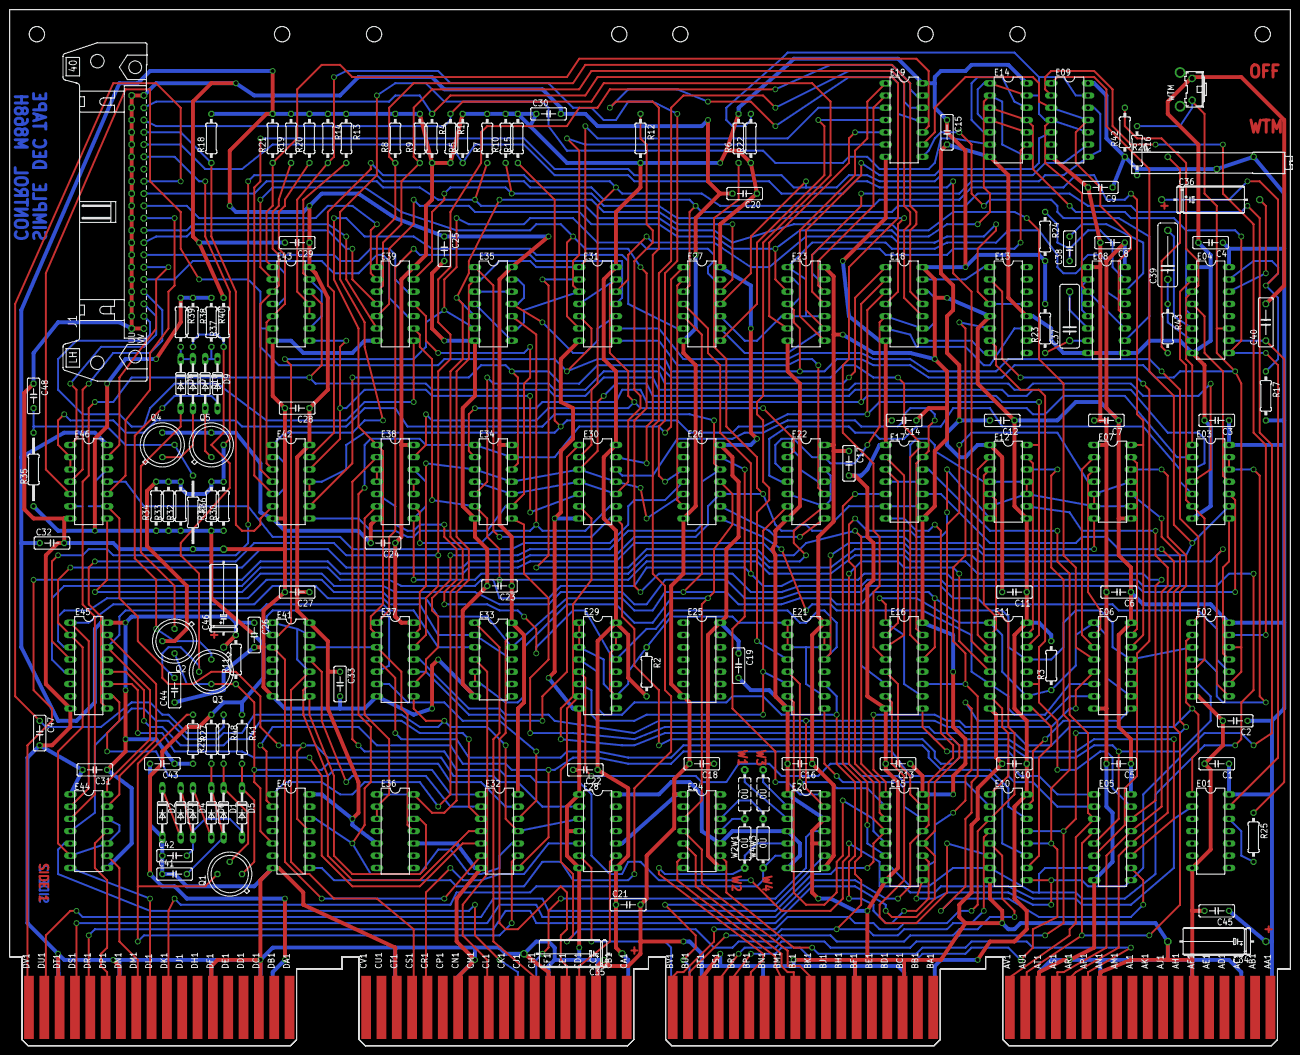
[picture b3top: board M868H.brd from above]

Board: 4 copper layers, 265.3 x 214.6 mm, 158 parts (0 on the bottom side), 222 nets.
